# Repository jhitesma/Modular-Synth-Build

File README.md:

# Modular Synth Build

Just a place for me to record information about the modular synth I'm building.  Documenting most of the build on the [LMNK Forum](https://lookmumnocomputer.discourse.group/t/my-first-diy-modules-starting-a-kosmo-format-build/1723?u=juggle).

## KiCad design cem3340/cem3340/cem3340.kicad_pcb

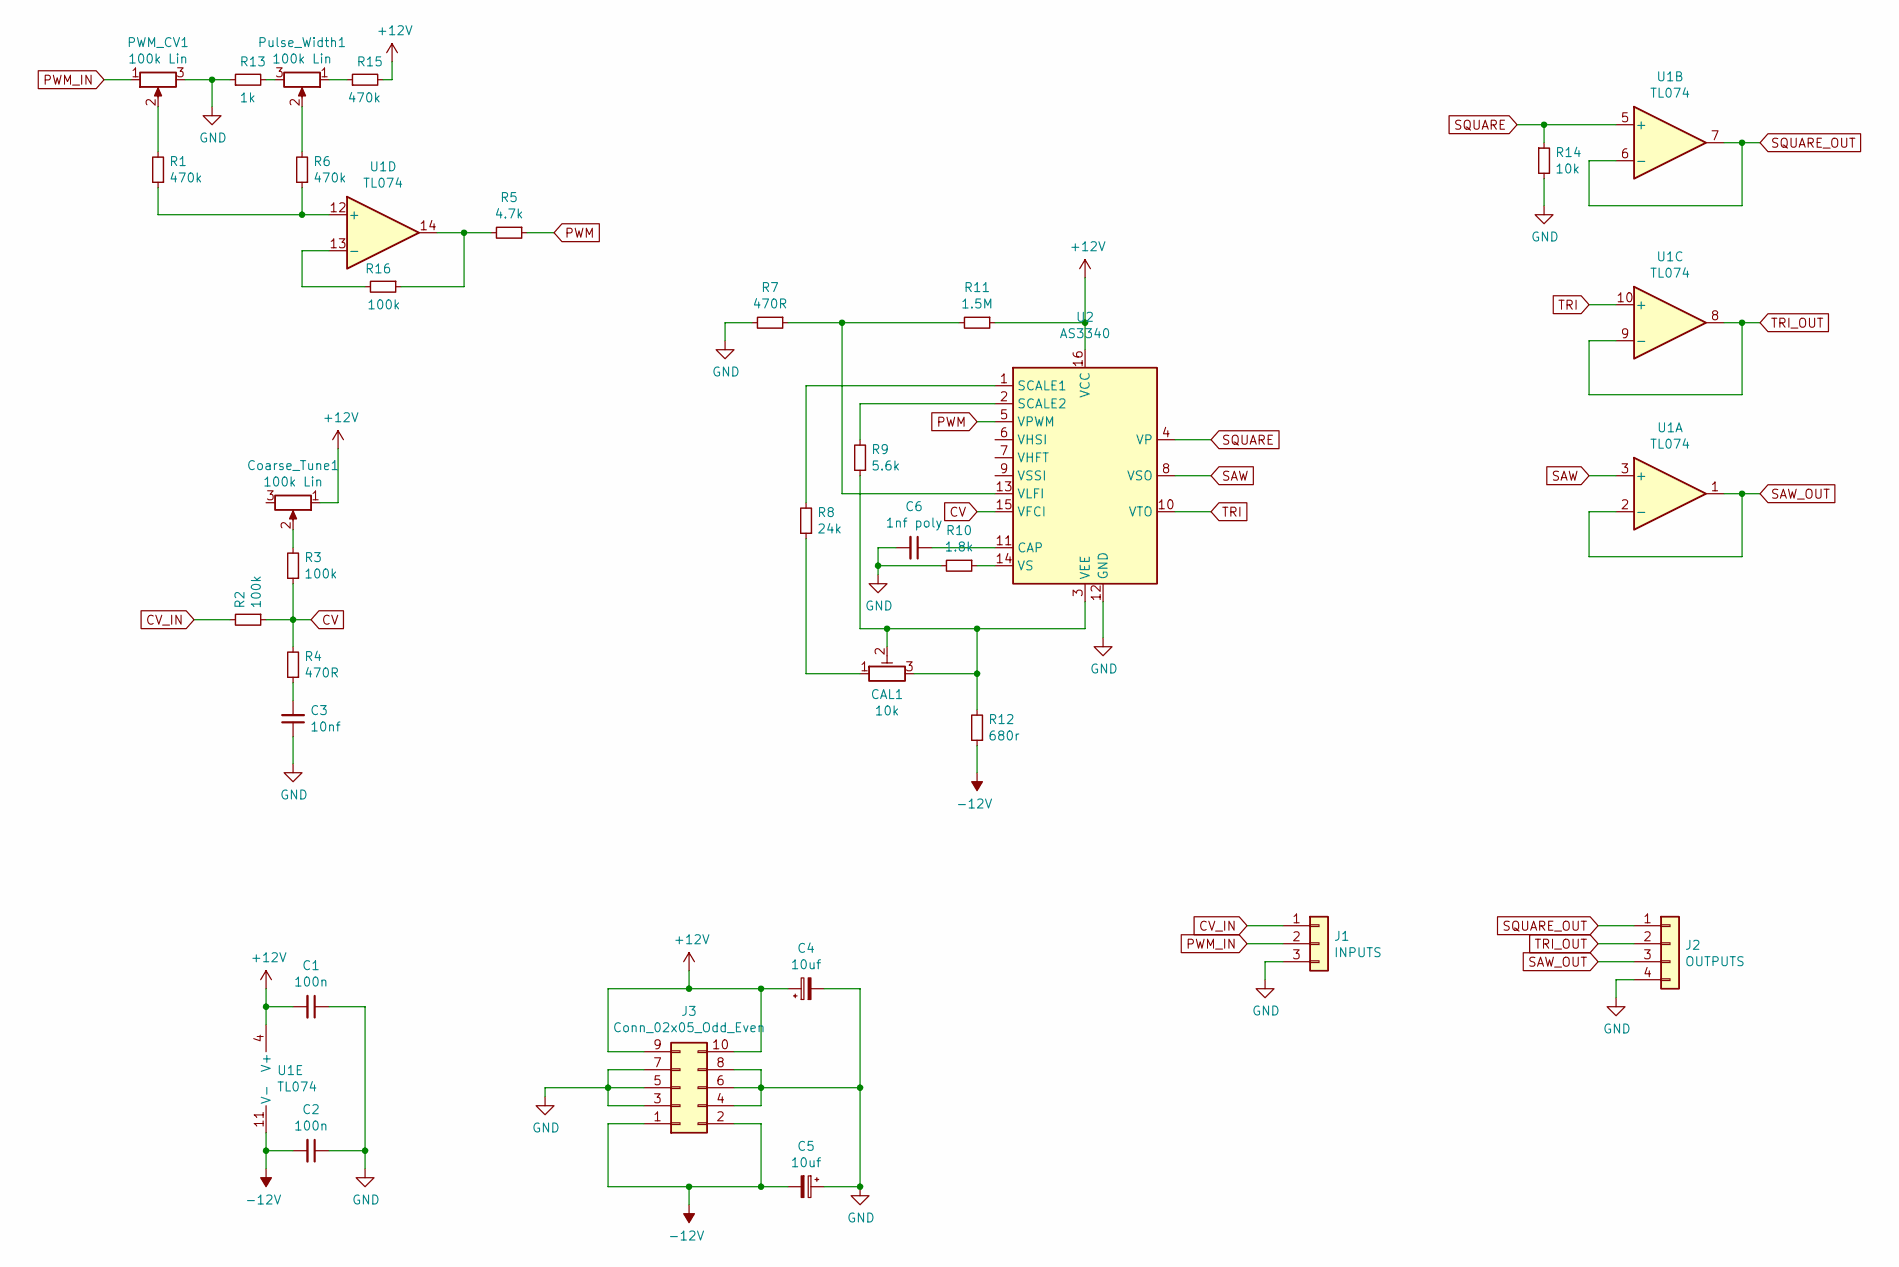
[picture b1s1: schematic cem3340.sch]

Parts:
C1, C2: 100n; C_Disc_D4.7mm_W2.5mm_P5.00mm
C3: 10nf; C_Disc_D4.7mm_W2.5mm_P5.00mm
C4, C5: 10uf; CP_Radial_D5.0mm_P2.50mm
C6: 1nf poly; C_Disc_D4.7mm_W2.5mm_P5.00mm
CAL1: 10k; Potentiometer_Bourns_3296W_Vertical
Coarse_Tune1: 100k Lin; JST_XH_B3B-XH-A_1x03_P2.50mm_Vertical
J1: INPUTS; JST_XH_B3B-XH-A_1x03_P2.50mm_Vertical
J2: OUTPUTS; JST_XH_B4B-XH-A_1x04_P2.50mm_Vertical
J3: Conn_02x05_Odd_Even; IDC-Header_2x05_P2.54mm_Vertical
PWM_CV1: 100k Lin; JST_XH_B3B-XH-A_1x03_P2.50mm_Vertical
Pulse_Width1: 100k Lin; JST_XH_B3B-XH-A_1x03_P2.50mm_Vertical
R1, R6, R15: 470k; R_Axial_DIN0207_L6.3mm_D2.5mm_P10.16mm_Horizontal
R2, R3, R16: 100k; R_Axial_DIN0207_L6.3mm_D2.5mm_P10.16mm_Horizontal
R4, R7: 470R; R_Axial_DIN0207_L6.3mm_D2.5mm_P10.16mm_Horizontal
R5: 4.7k; R_Axial_DIN0207_L6.3mm_D2.5mm_P10.16mm_Horizontal
R8: 24k; R_Axial_DIN0207_L6.3mm_D2.5mm_P10.16mm_Horizontal
R9: 5.6k; R_Axial_DIN0207_L6.3mm_D2.5mm_P10.16mm_Horizontal
R10: 1.8k; R_Axial_DIN0207_L6.3mm_D2.5mm_P10.16mm_Horizontal
R11: 1.5M; R_Axial_DIN0207_L6.3mm_D2.5mm_P10.16mm_Horizontal
R12: 680r; R_Axial_DIN0207_L6.3mm_D2.5mm_P10.16mm_Horizontal
R13: 1k; R_Axial_DIN0207_L6.3mm_D2.5mm_P10.16mm_Horizontal
R14: 10k; R_Axial_DIN0207_L6.3mm_D2.5mm_P10.16mm_Horizontal
U1: TL074; DIP-14_W7.62mm_Socket_LongPads
U2: AS3340; DIP-16_W7.62mm_Socket_LongPads

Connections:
+12V: C1.2, C4.1, Coarse_Tune1.1, J3.9, J3.10, R11.1, R15.2, U1.4 (V+), U2.16 (VCC)
-12V: C2.2, C5.2, J3.1, J3.2, R12.1, U1.11 (V-)
CV: R2.1, R3.1, R4.2, U2.15 (VFCI)
CV_IN: J1.1, R2.2
GND: C1.1, C2.1, C3.1, C4.2, C5.1, C6.2, J1.3, J2.4, J3.3, J3.4, J3.5, J3.6, J3.7, J3.8, PWM_CV1.3, R7.2, R10.2, R13.1, R14.2, U2.12 (GND)
unnamed: C3.2, R4.1
unnamed: C6.1, U2.11 (CAP)
unnamed: CAL1.1, R8.1
unnamed: CAL1.2, CAL1.3, R9.1, R12.2, U2.3 (VEE)
unnamed: Coarse_Tune1.2, R3.2
unnamed: PWM_CV1.2, R1.2
unnamed: Pulse_Width1.1, R15.1
unnamed: Pulse_Width1.2, R6.2
unnamed: Pulse_Width1.3, R13.2
unnamed: R1.1, R6.1, U1.12 (+)
unnamed: R8.2, U2.1 (SCALE1)
unnamed: R9.2, U2.2 (SCALE2)
unnamed: R10.1, U2.14 (VS)
unnamed: R7.1, R11.2, U2.13 (VLFI)
unnamed: R5.2, R16.1, U1.14
unnamed: R16.2, U1.13 (-)
PWM: R5.1, U2.5 (VPWM)
PWM_IN: J1.2, PWM_CV1.1
SAW: U1.3 (+), U2.8 (VSO)
SAW_OUT: J2.3, U1.1, U1.2 (-)
SQUARE: R14.1, U1.5 (+), U2.4 (VP)
SQUARE_OUT: J2.1, U1.6 (-), U1.7
TRI: U1.10 (+), U2.10 (VTO)
TRI_OUT: J2.2, U1.8, U1.9 (-)

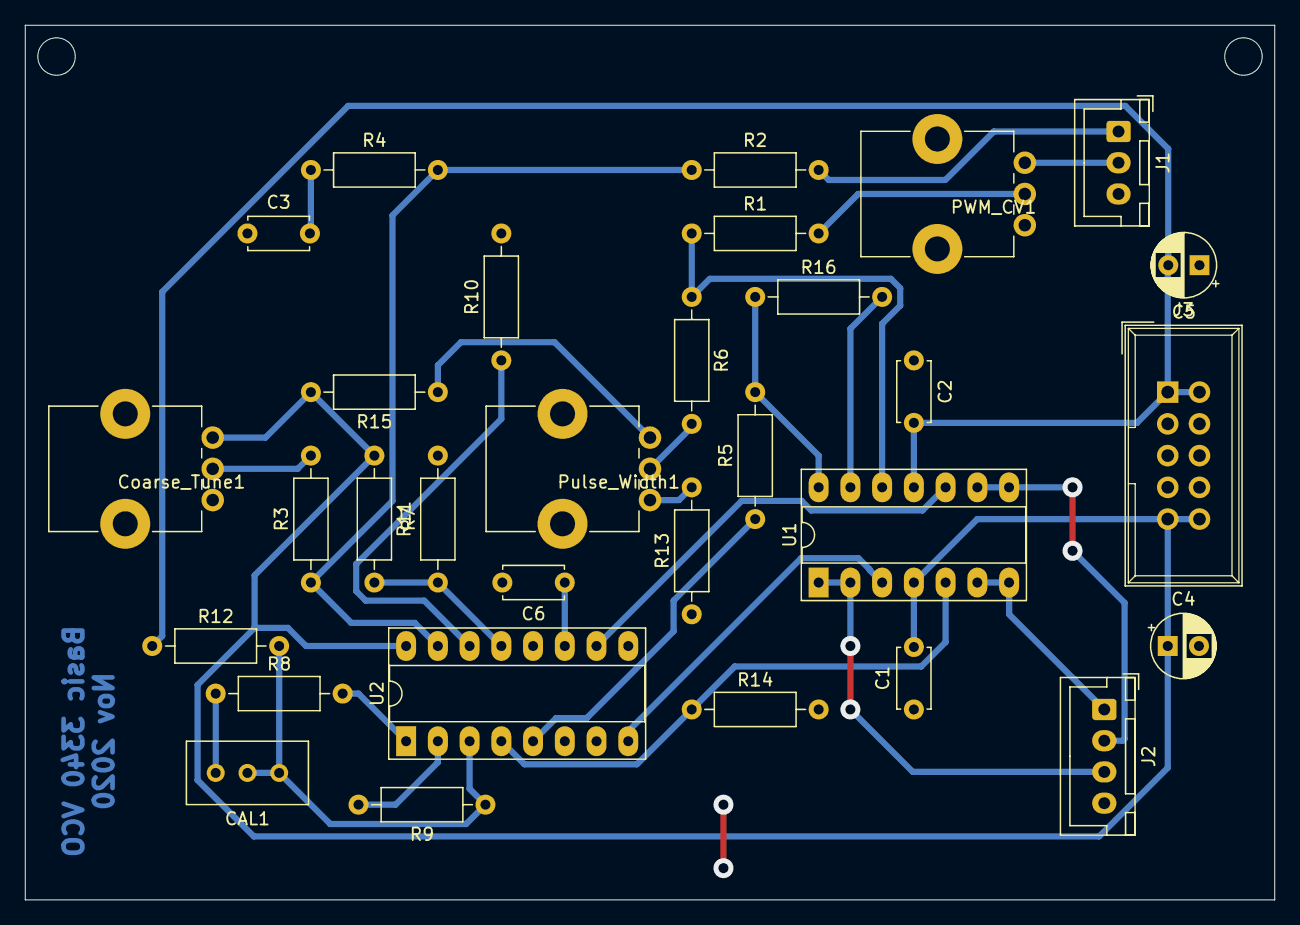
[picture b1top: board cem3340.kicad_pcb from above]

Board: 2 copper layers, 100.0 x 70.0 mm, 31 parts (0 on the bottom side), 29 nets.

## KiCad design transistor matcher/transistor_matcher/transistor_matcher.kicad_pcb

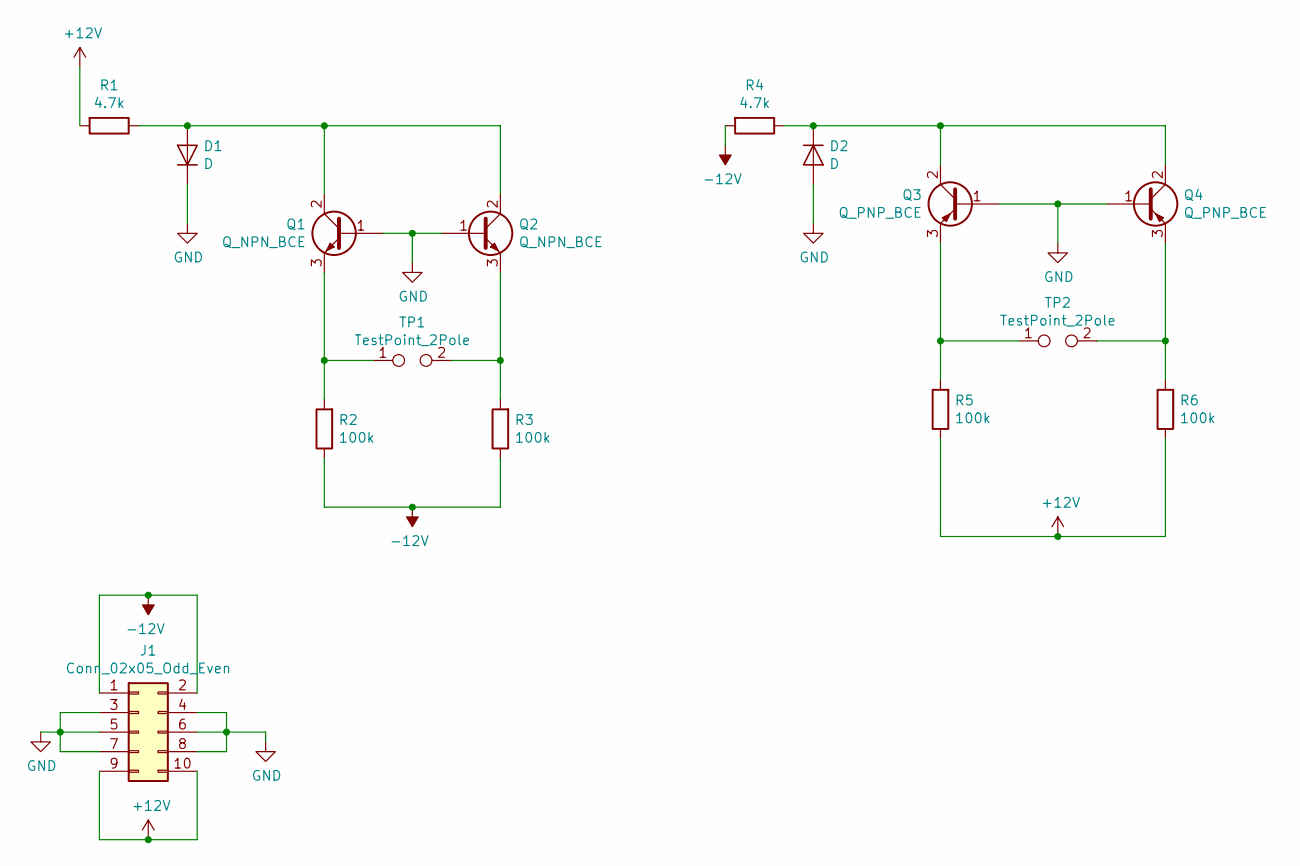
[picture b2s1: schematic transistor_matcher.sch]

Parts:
D1, D2: D; D_DO-34_SOD68_P7.62mm_Horizontal
J1: Conn_02x05_Odd_Even; IDC-Header_2x05_P2.54mm_Vertical
Q1, Q2: Q_NPN_BCE; TO-92L_Inline_Wide
Q3, Q4: Q_PNP_BCE; TO-92L_Inline_Wide
R1, R4: 4.7k; R_Axial_DIN0204_L3.6mm_D1.6mm_P7.62mm_Horizontal
R2, R3, R5, R6: 100k; R_Axial_DIN0204_L3.6mm_D1.6mm_P7.62mm_Horizontal
TP1, TP2: TestPoint_2Pole; PinHeader_1x02_P2.54mm_Vertical

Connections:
+12V: J1.9, J1.10, R1.2, R5.1, R6.1
-12V: J1.1, J1.2, R2.1, R3.1, R4.2
GND: D1.1 (K), D2.2 (A), J1.3, J1.4, J1.5, J1.6, J1.7, J1.8, Q1.1 (B), Q2.1 (B), Q3.1 (B), Q4.1 (B)
unnamed: D1.2 (A), Q1.2 (C), Q2.2 (C), R1.1
unnamed: D2.1 (K), Q3.2 (C), Q4.2 (C), R4.1
unnamed: Q1.3 (E), R2.2, TP1.1
unnamed: Q2.3 (E), R3.2, TP1.2
unnamed: Q3.3 (E), R5.2, TP2.1
unnamed: Q4.3 (E), R6.2, TP2.2

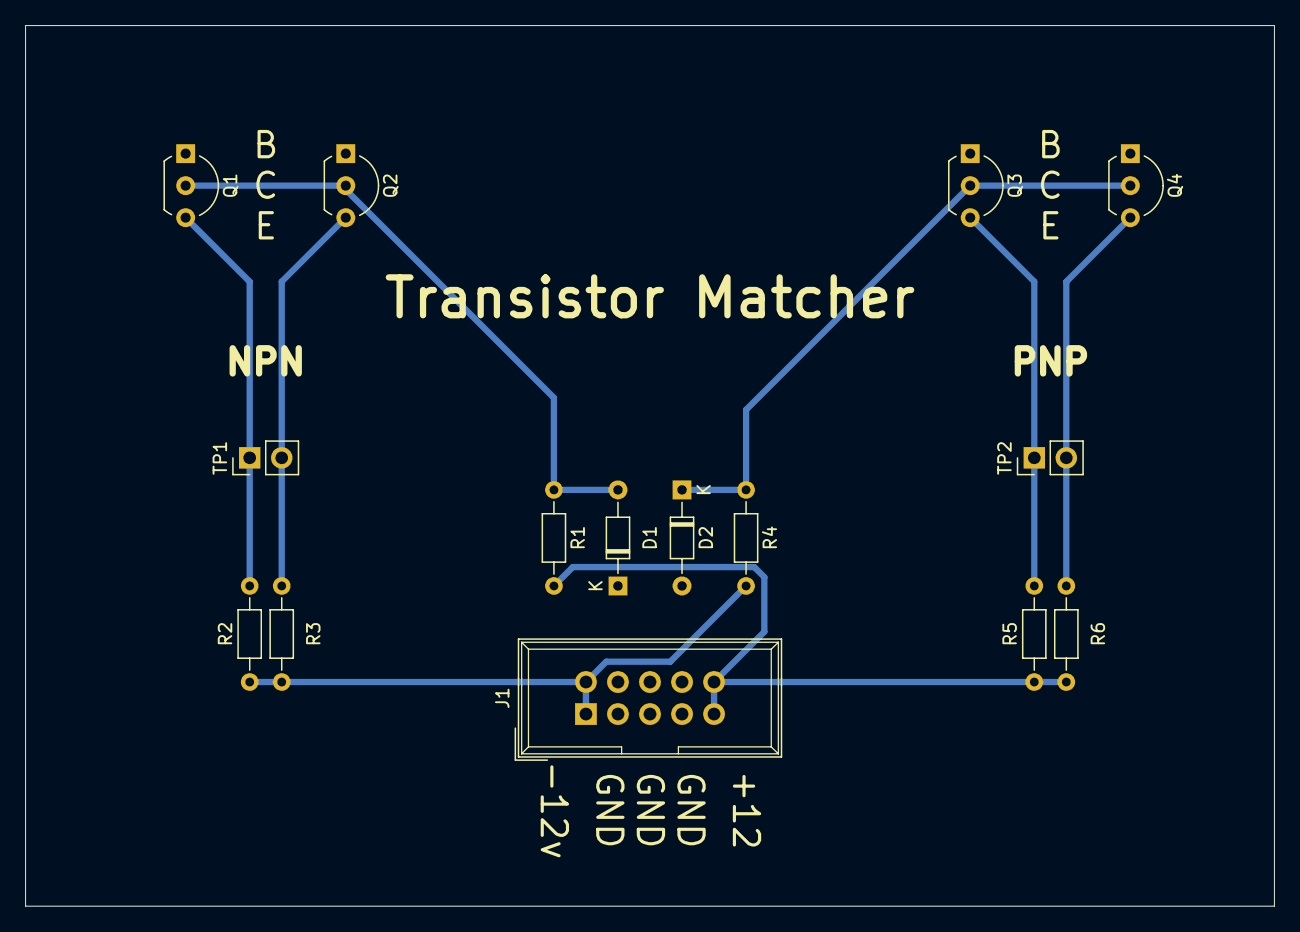
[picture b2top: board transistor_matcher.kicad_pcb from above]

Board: 2 copper layers, 99.1 x 69.9 mm, 15 parts (0 on the bottom side), 9 nets.

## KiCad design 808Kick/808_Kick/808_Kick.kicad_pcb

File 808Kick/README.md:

# M4TM 808 Kick

Based on a [schematic by Juanito Moore](080 schematic.JPG) (included here for reference) in his youtube video: https://www.youtube.com/watch?v=xPBeEi4SE68  Be sure to check out his great video where he shows another way to build the circuit and explains it's working in detail.

I drew up a PCB in Kicad and etched it myself mostly as an excuse to learn how.  I used UV dry transfer film and transfered my layout by printing it inverted on vellum to make a negative.  Took me a few tries to get the process down but was able to etch this board successfully and get it working.

Note: The version I built and show in the photo above is different than what I'm including.  After buidling it I made two small changes eliminating the need for the two black jumpers on the back of the board pictured above.  Also the red jumper was to fix a trace I damaged when drilling the board.  The only jumpers this board should need are on the front and shows as front traces in the Kicad files.

No gerbers included but you should be able to export them from kicad easily enough.  I did include the exported PDF's and Photoshop files I used to prepare my negative for etching

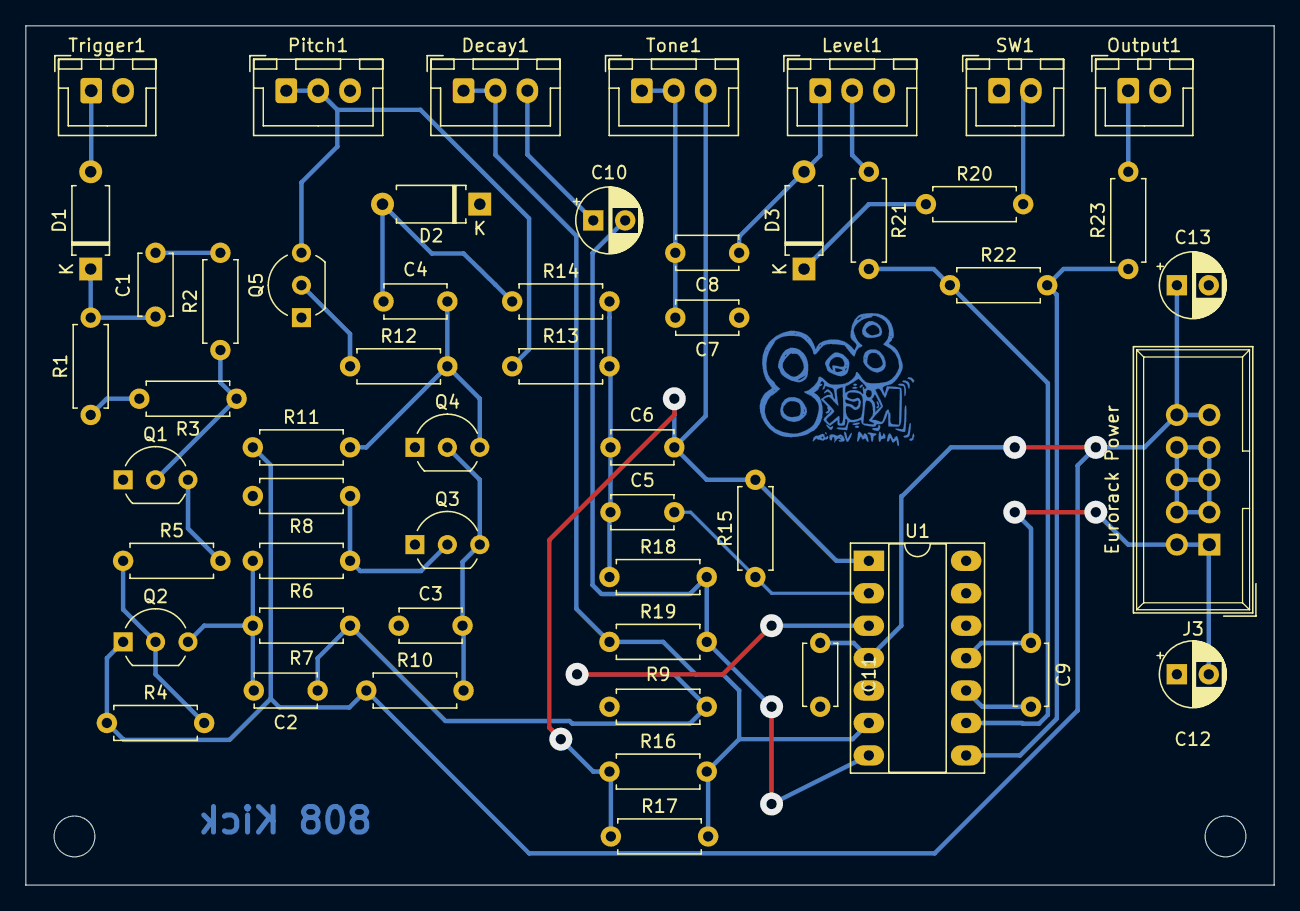
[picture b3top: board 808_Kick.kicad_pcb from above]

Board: 2 copper layers, 97.8 x 67.3 mm, 53 parts (0 on the bottom side), 32 nets.

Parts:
C1, C3, C7, C9, C11: 100n; C_Disc_D4.7mm_W2.5mm_P5.00mm
C2, C5, C6: 15n; C_Disc_D4.7mm_W2.5mm_P5.00mm
C4: 33n; C_Disc_D4.7mm_W2.5mm_P5.00mm
C8: 470n; C_Disc_D4.7mm_W2.5mm_P5.00mm
C10: 33u; CP_Radial_D5.0mm_P2.50mm
C12, C13: 10uf; CP_Radial_D5.0mm_P2.50mm
D1, D2, D3: D; D_A-405_P7.62mm_Horizontal
Decay1: 500K; JST_XH_B3B-XH-A_1x03_P2.50mm_Vertical
J3: Eurorack Power; IDC-Header_2x05_P2.54mm_Vertical
Level1: 10K; JST_XH_B3B-XH-A_1x03_P2.50mm_Vertical
Output1: Output; JST_XH_B2B-XH-A_1x02_P2.50mm_Vertical
Pitch1: 100K; JST_XH_B3B-XH-A_1x03_P2.50mm_Vertical
Q1, Q3, Q4, Q5: 2N3904; TO-92_Inline_Wide
Q2: 2N3906; TO-92_Inline_Wide
R1, R7, R12: 100K; R_Axial_DIN0207_L6.3mm_D2.5mm_P7.62mm_Horizontal
R2, R11: 22K; R_Axial_DIN0207_L6.3mm_D2.5mm_P7.62mm_Horizontal
R3, R4, R5, R21: 10K; R_Axial_DIN0207_L6.3mm_D2.5mm_P7.62mm_Horizontal
R6: 8.2K; R_Axial_DIN0207_L6.3mm_D2.5mm_P7.62mm_Horizontal
R8: 2.7K; R_Axial_DIN0207_L6.3mm_D2.5mm_P7.62mm_Horizontal
R9: 4.7K; R_Axial_DIN0207_L6.3mm_D2.5mm_P7.62mm_Horizontal
R10, R14, R15: 1M; R_Axial_DIN0207_L6.3mm_D2.5mm_P7.62mm_Horizontal
R13: 6.8K; R_Axial_DIN0207_L6.3mm_D2.5mm_P7.62mm_Horizontal
R16: 330K; R_Axial_DIN0207_L6.3mm_D2.5mm_P7.62mm_Horizontal
R17, R19: 47K; R_Axial_DIN0207_L6.3mm_D2.5mm_P7.62mm_Horizontal
R18: 470K; R_Axial_DIN0207_L6.3mm_D2.5mm_P7.62mm_Horizontal
R20, R23: 680R; R_Axial_DIN0207_L6.3mm_D2.5mm_P7.62mm_Horizontal
R22: 20K; R_Axial_DIN0207_L6.3mm_D2.5mm_P7.62mm_Horizontal
SW1: Clipper; JST_XH_B2B-XH-A_1x02_P2.50mm_Vertical
Tone1: 5K; JST_XH_B3B-XH-A_1x03_P2.50mm_Vertical
Trigger1: Trigger; JST_XH_B2B-XH-A_1x02_P2.50mm_Vertical
U1: TL074; DIP-14_W7.62mm_Socket_LongPads

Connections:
+VDC: C11.2, C13.1, J3.9, J3.10, Q2.1, R4.1, R10.1, R11.1, U1.4
-VDC: C9.2, C12.2, J3.1, J3.2, U1.11
GND: C3.1, C7.1, C9.1, C11.1, C12.1, C13.2, D2.1, J3.3, J3.4, J3.5, J3.6, J3.7, J3.8, Level1.3, Output1.2, Pitch1.3, Q1.1, Q3.1, Q4.1, Q5.1, R1.1, R3.2, R8.2, R9.2, SW1.1, Trigger1.2, U1.5, U1.10, U1.12
unnamed: C1.1, R2.2
unnamed: C1.2, D1.1, R1.2
unnamed: C2.1, R7.2, R9.1, U1.3
unnamed: C2.2, Q2.3, R6.2, R7.1
unnamed: C3.2, Q3.3, Q4.2, R10.2
unnamed: C4.1, D2.2, R14.1
unnamed: C4.2, Q4.3, R11.2, R12.2
unnamed: C5.1, C6.2, R13.2, R14.2, R18.1
unnamed: C5.2, R15.1, U1.2
unnamed: C6.1, R15.2, R16.1, R17.1, Tone1.3, U1.1
unnamed: C7.2, C8.2, Tone1.1, Tone1.2
unnamed: C8.1, D3.2, Level1.1
unnamed: C10.1, Decay1.3
unnamed: C10.2, R18.2, R19.2, U1.7
unnamed: D3.1, R20.1
unnamed: Decay1.1, Decay1.2, R16.2, R17.2, R19.1, U1.6
unnamed: Level1.2, R21.1
unnamed: Pitch1.1, Pitch1.2, Q5.3, R13.1
unnamed: Q1.2, R2.1, R3.1
unnamed: Q1.3, R5.2
unnamed: Q2.2, R4.2, R5.1
unnamed: Q3.2, R6.1, R8.1
unnamed: Q5.2, R12.1
unnamed: R20.2, SW1.2
unnamed: R21.2, R22.1, U1.9
unnamed: R22.2, R23.1, U1.8
unnamed: U1.13, U1.14
Output: Output1.1, R23.2
Trigger: D1.2, Trigger1.1

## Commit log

2020-09-16 Initial project organization
2020-09-20 Add 6mm two part knob
2020-09-20 The MIAW LM13700 dual VCA
2020-09-21 Updates to the mixer
    Add 3D printing files
    Minor layout improvements
    Add board with no components image showing trace cuts
2020-09-21 New Panel for simple LFO
2020-09-21 A few images of the Dual VCA
2020-09-21 Two photos of the mixer
2020-09-24 New panel for MS-20
2020-09-24 New panel for noise drum
2020-09-27 Added Clock Divider
2020-09-27 Added Readme to clock divider
2020-09-27 Fix typo
2020-09-28 reference schematic for simple LFO
2020-10-23 Add M4TM 808 kick files
2020-10-23 Add files for Midibox CV/Outputs interfaces
2020-10-23 Missed a few changes on the 808 Kick
2020-11-02 Add working files for transistor matching PCB
2020-11-03 Updates to transistor matcher
2020-11-05 Move transistor matcher to it's own repo
2020-11-22 Simple 3340 VCO
2020-11-22 Add gerbers for 3340 VCO
2022-05-09 Set theme jekyll-theme-tactile
